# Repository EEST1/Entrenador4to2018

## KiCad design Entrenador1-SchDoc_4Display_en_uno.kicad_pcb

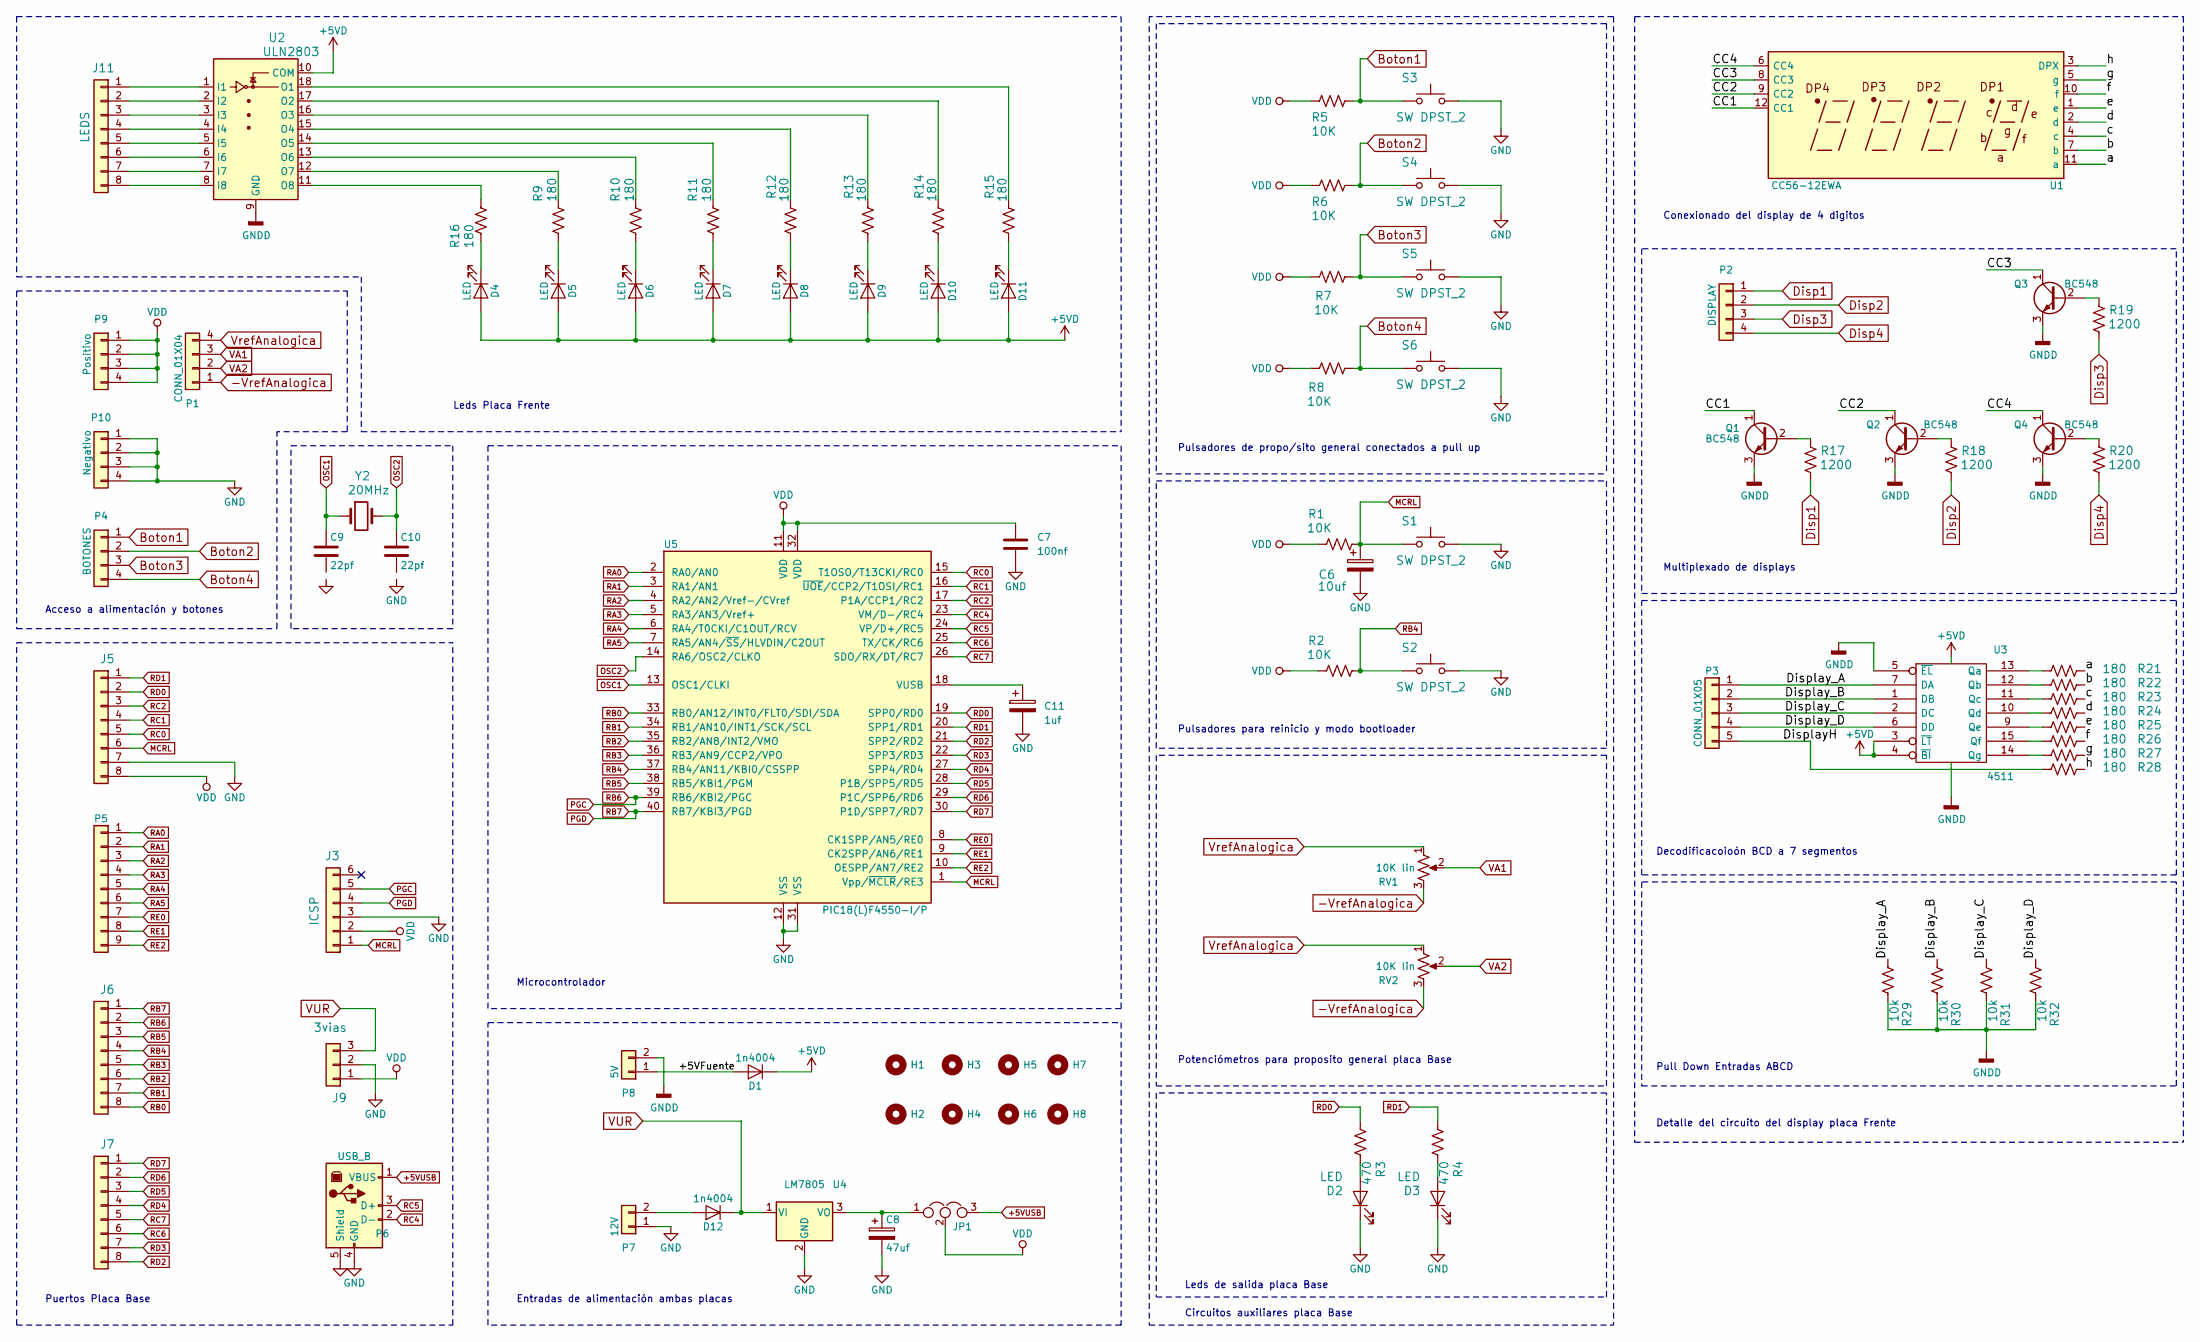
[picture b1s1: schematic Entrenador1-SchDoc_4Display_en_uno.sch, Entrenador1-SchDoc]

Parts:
C6: 10uf; CP_Radial_D6.3mm_P2.50mm
C7: 100nf; C_Disc_D5.0mm_W2.5mm_P2.50mm
C8: 47uf; CP_Radial_D5.0mm_P2.50mm
C9, C10: 22pf; C_Disc_D5.0mm_W2.5mm_P2.50mm
C11: 1uf; CP_Radial_D5.0mm_P2.50mm
D1, D12: 1n4004; D_5W_P10.16mm_Horizontal
D2, D3, D4, D5, D6, D7, D8, D9, D10, D11: LED; LED_D3.0mm
H1, H2, H3, H4, H5, H6, H7, H8: MountingHole; MountingHole_3.2mm_M3
J3: ICSP; Socket_Strip_Straight_1x06_Pitch2.54mm
J5, J6, J7: CON8; Socket_Strip_Straight_1x08_Pitch2.54mm
J9: 3vias; Pin_Header_Straight_1x03_Pitch2.54mm
J11: LEDS; Socket_Strip_Straight_1x08_Pitch2.54mm
JP1: JUMPER3; Pin_Header_Straight_1x03_Pitch2.54mm
P1: CONN_01X04; Socket_Strip_Straight_1x04_Pitch2.54mm
P2: DISPLAY; Socket_Strip_Straight_1x04_Pitch2.54mm
P3: CONN_01X05; Socket_Strip_Straight_1x05_Pitch2.54mm
P4: BOTONES; Socket_Strip_Straight_1x04_Pitch2.54mm
P5: CONN_01X09; Socket_Strip_Straight_1x09_Pitch2.54mm
P6: USB_B
P7: 12V; TerminalBlock_bornier-2_P5.08mm
P8: 5V; TerminalBlock_bornier-2_P5.08mm
P9: Positivo; Socket_Strip_Straight_1x04_Pitch2.54mm
P10: Negativo; Socket_Strip_Straight_1x04_Pitch2.54mm
Q1, Q2, Q3, Q4: BC548; TO-92_Molded_Narrow
R1, R2, R5, R6, R7, R8: 10K; R_Axial_DIN0207_L6.3mm_D2.5mm_P7.62mm_Horizontal
R3, R4: 470; R_Axial_DIN0207_L6.3mm_D2.5mm_P7.62mm_Horizontal
R9, R10, R11, R12, R13, R14, R15, R16, R21, R22, R23, R24, R25, R26, R27, R28: 180; R_Axial_DIN0207_L6.3mm_D2.5mm_P7.62mm_Horizontal
R17, R18, R19, R20: 1200; R_Axial_DIN0207_L6.3mm_D2.5mm_P7.62mm_Horizontal
R29, R30, R31, R32: 10k; R_Axial_DIN0207_L6.3mm_D2.5mm_P7.62mm_Horizontal
RV1, RV2: 10K lin; Potentiometer_Omeg_PC16PU_Horizontal
S1, S2, S3, S4, S5, S6: SW DPST_2; SW_PUSH_6mm_h13mm
U1: CC56-12EWA; CA56-12EWA
U2: ULN2803; DIP-18_W7.62mm_LongPads
U3: 4511; DIP-16_W7.62mm
U4: LM7805; TO-220-3_Vertical
U5: PIC18(L)F4550-I/P; DIP-40_W15.24mm_LongPads
Y2: 20MHz; Crystal_HC49-4H_Vertical

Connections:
+5VD: D1.1 (K), D4.2 (A), D5.2 (A), D6.2 (A), D7.2 (A), D8.2 (A), D9.2 (A), D10.2 (A), D11.2 (A), U2.10 (COM), U3.3 (~LT), U3.4 (~BI), U3.16 (Vdd)
+5VUSB: JP1.3, P6.1 (VBUS)
-VrefAnalogica: P1.1, RV1.3, RV2.3
/+5VFuente: D1.2 (A), P8.1
/CC1: Q1.1 (C), U1.12 (CC1)
/CC2: Q2.1 (C), U1.9 (CC2)
/CC3: Q3.1 (C), U1.8 (CC3)
/CC4: Q4.1 (C), U1.6 (CC4)
/DisplayH: P3.5, R28.2
/Display_A: P3.1, R29.1, U3.7 (DA)
/Display_B: P3.2, R30.1, U3.1 (DB)
/Display_C: P3.3, R31.1, U3.2 (DC)
/Display_D: P3.4, R32.1, U3.6 (DD)
/a: R21.1, U1.11 (a)
/b: R22.1, U1.7 (b)
/c: R23.1, U1.4 (c)
/d: R24.1, U1.2 (d)
/e: R25.1, U1.1 (e)
/f: R26.1, U1.10 (f)
/g: R27.1, U1.5 (g)
/h: R28.1, U1.3 (DPX)
Boton1: P4.1, R5.2, S3.1
Boton2: P4.2, R6.2, S4.1
Boton3: P4.3, R7.1, S5.1
Boton4: P4.4, R8.1, S6.1
Disp1: P2.1, R17.2
Disp2: P2.2, R18.2
Disp3: P2.3, R19.2
Disp4: P2.4, R20.2
GND: C6.2, C7.2, C8.2, C11.2, D2.1 (K), D3.1 (K), J3.3, J5.7, J9.2, P6.4 (GND), P6.5 (Shield), P7.1, P10.1, P10.2, P10.3, P10.4, S1.2, S2.2, S3.2, S4.2, S5.2, S6.2, U4.2 (GND), U5.12 (VSS), U5.31 (VSS)
GNDD: P8.2, Q1.3 (E), Q2.3 (E), Q3.3 (E), Q4.3 (E), R29.2, R30.2, R31.2, R32.2, U2.9 (GND), U3.5 (~EL), U3.8 (Vss)
MCRL: C6.1, J3.1, J5.6, R1.1, S1.1, U5.1 (Vpp/~MCLR~/RE3)
unnamed: C8.1, JP1.1, U4.3 (VO)
unnamed: C11.1, U5.18 (VUSB)
unnamed: D2.2 (A), R3.2
unnamed: D3.2 (A), R4.2
unnamed: D4.1 (K), R16.1
unnamed: D5.1 (K), R9.1
unnamed: D6.1 (K), R10.1
unnamed: D7.1 (K), R11.1
unnamed: D8.1 (K), R12.1
unnamed: D9.1 (K), R13.1
unnamed: D10.1 (K), R14.1
unnamed: D11.1 (K), R15.1
unnamed: D12.2 (A), P7.2
unnamed: J11.1, U2.1 (I1)
unnamed: J11.2, U2.2 (I2)
unnamed: J11.3, U2.3 (I3)
unnamed: J11.4, U2.4 (I4)
unnamed: J11.5, U2.5 (I5)
unnamed: J11.6, U2.6 (I6)
unnamed: J11.7, U2.7 (I7)
unnamed: J11.8, U2.8 (I8)
unnamed: Q1.2 (B), R17.1
unnamed: Q2.2 (B), R18.1
unnamed: Q3.2 (B), R19.1
unnamed: Q4.2 (B), R20.1
unnamed: R9.2, U2.12 (O7)
unnamed: R10.2, U2.13 (O6)
unnamed: R11.2, U2.14 (O5)
unnamed: R12.2, U2.15 (O4)
unnamed: R13.2, U2.16 (O3)
unnamed: R14.2, U2.17 (O2)
unnamed: R15.2, U2.18 (O1)
unnamed: R16.2, U2.11 (O8)
unnamed: R21.2, U3.13 (Qa)
unnamed: R22.2, U3.12 (Qb)
unnamed: R23.2, U3.11 (Qc)
unnamed: R24.2, U3.10 (Qd)
unnamed: R25.2, U3.9 (Qe)
unnamed: R26.2, U3.15 (Qf)
unnamed: R27.2, U3.14 (Qg)
OSC1: C9.1, U5.13 (OSC1/CLKI), Y2.1
OSC2: C10.1, U5.14 (RA6/OSC2/CLKO), Y2.2
PGC: J3.5, J6.2, U5.39 (RB6/KBI2/PGC)
PGD: J3.4, J6.1, U5.40 (RB7/KBI3/PGD)
RA0: P5.1, U5.2 (RA0/AN0)
RA1: P5.2, U5.3 (RA1/AN1)
RA2: P5.3, U5.4 (RA2/AN2/Vref-/CVref)
RA3: P5.4, U5.5 (RA3/AN3/Vref+)
RA4: P5.5, U5.6 (RA4/T0CKI/C1OUT/RCV)
RA5: P5.6, U5.7 (RA5/AN4/~SS~/HLVDIN/C2OUT)
RB0: J6.8, U5.33 (RB0/AN12/INT0/FLT0/SDI/SDA)
RB1: J6.7, U5.34 (RB1/AN10/INT1/SCK/SCL)
RB2: J6.6, U5.35 (RB2/AN8/INT2/VMO)
RB3: J6.5, U5.36 (RB3/AN9/CCP2/VPO)
RB4: J6.4, R2.1, S2.1, U5.37 (RB4/AN11/KBI0/CSSPP)
RB5: J6.3, U5.38 (RB5/KBI1/PGM)
RC0: J5.5, U5.15 (T1OSO/T13CKI/RC0)
RC1: J5.4, U5.16 (~UOE~/CCP2/T1OSI/RC1)
RC2: J5.3, U5.17 (P1A/CCP1/RC2)
RC4: P6.2 (D-), U5.23 (VM/D-/RC4)
RC5: P6.3 (D+), U5.24 (VP/D+/RC5)
RC6: J7.6, U5.25 (TX/CK/RC6)
RC7: J7.5, U5.26 (SDO/RX/DT/RC7)
RD0: J5.2, R3.1, U5.19 (SPP0/RD0)
RD1: J5.1, R4.1, U5.20 (SPP1/RD1)
RD2: J7.8, U5.21 (SPP2/RD2)
RD3: J7.7, U5.22 (SPP3/RD3)
RD4: J7.4, U5.27 (SPP4/RD4)
RD5: J7.3, U5.28 (P1B/SPP5/RD5)
RD6: J7.2, U5.29 (P1C/SPP6/RD6)
RD7: J7.1, U5.30 (P1D/SPP7/RD7)
RE0: P5.7, U5.8 (CK1SPP/AN5/RE0)
RE1: P5.8, U5.9 (CK2SPP/AN6/RE1)
RE2: P5.9, U5.10 (OESPP/AN7/RE2)
VA1: P1.3, RV1.2
VA2: P1.2, RV2.2
VDD: C7.1, J3.2, J5.8, J9.1, JP1.2, P9.1, P9.2, P9.3, P9.4, R1.2, R2.2, R5.1, R6.1, R7.2, R8.2, U5.11 (VDD), U5.32 (VDD)
VUR: D12.1 (K), J9.3, U4.1 (VI)
VrefAnalogica: P1.4, RV1.1, RV2.1

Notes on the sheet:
Decodificacoioón BCD a 7 segmentos
Pull Down Entradas ABCD
Pulsadores de propo/sito general conectados a pull up
Pulsadores para reinicio y modo bootloader
Potenciómetros para proposito general placa Base
Puertos Placa Base
Multiplexado de displays
Conexionado del display de 4 digitos
Entradas de alimentación ambas placas
Leds de salida placa Base
Acceso a alimentación y botones
Microcontrolador
Leds Placa Frente
Detalle del circuito del display placa Frente
Circuitos auxiliares placa Base

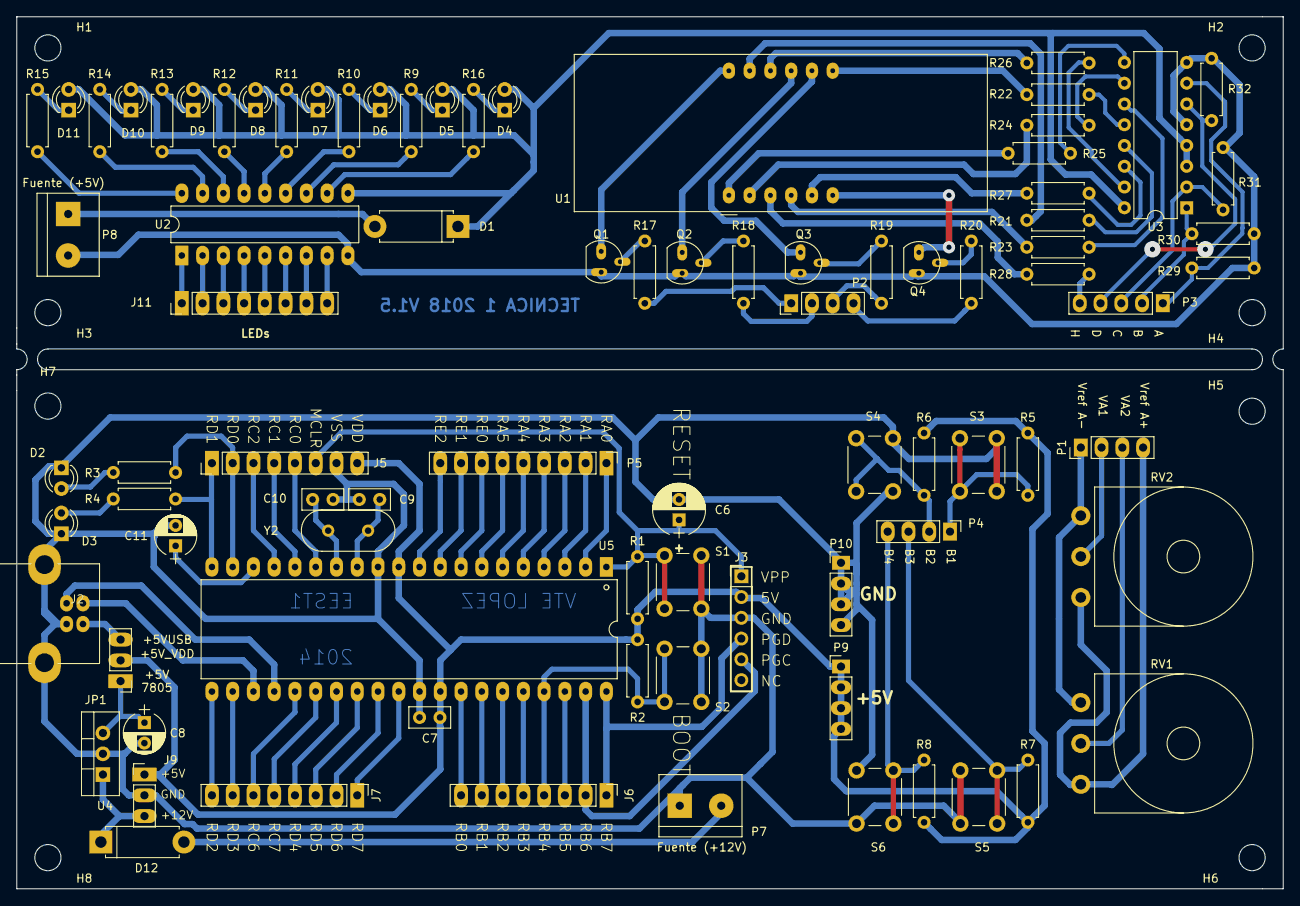
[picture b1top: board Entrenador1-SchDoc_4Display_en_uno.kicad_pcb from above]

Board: 2 copper layers, 154.9 x 106.7 mm, 93 parts (0 on the bottom side), 111 nets.

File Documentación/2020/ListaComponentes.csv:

Referencia,Cantidad,Value,Footprint
C10 C9,2,22pf,C_Disc_D5.0mm_W2.5mm_P2.50mm
C11,1,1uf,CP_Radial_D5.0mm_P2.50mm
C6,1,10uf,CP_Radial_D6.3mm_P2.50mm
C7,1,100nf,C_Disc_D5.0mm_W2.5mm_P2.50mm
C8,1,47uf,CP_Radial_D5.0mm_P2.50mm
D1 D12,2,1n4004,D_5W_P10.16mm_Horizontal
D11 D10 D9 D8 D7 D6 D5 D4 D3 D2,10,LED,LED_D3.0mm
J11,1,LEDS,Socket_Strip_Straight_1x08_Pitch2.54mm
J3,1,ICSP,Socket_Strip_Straight_1x06_Pitch2.54mm
J5 J6 J7,3,CON8,Socket_Strip_Straight_1x08_Pitch2.54mm
J9,1,3vias,Pin_Header_Straight_1x03_Pitch2.54mm
JP1,1,JUMPER3,Pin_Header_Straight_1x03_Pitch2.54mm
P1,1,CONN_01X04,Socket_Strip_Straight_1x04_Pitch2.54mm
P10,1,Negativo,Socket_Strip_Straight_1x04_Pitch2.54mm
P2,1,DISPLAY,Socket_Strip_Straight_1x04_Pitch2.54mm
P3,1,CONN_01X05,Socket_Strip_Straight_1x05_Pitch2.54mm
P4,1,BOTONES,Socket_Strip_Straight_1x04_Pitch2.54mm
P5,1,CONN_01X09,Socket_Strip_Straight_1x09_Pitch2.54mm
P6,1,USB_B,USB_B
P7,1,12V,TerminalBlock_bornier-2_P5.08mm
P8,1,5V,TerminalBlock_bornier-2_P5.08mm
P9,1,Positivo,Socket_Strip_Straight_1x04_Pitch2.54mm
Q4 Q3 Q2 Q1,4,BC548,TO-92_Molded_Narrow
R20 R19 R18 R17,4,1200,R_Axial_DIN0207_L6.3mm_D2.5mm_P7.62mm_Horizontal
R27 R26 R25 R24 R23 R22 R21 R16 R15 R14 R13 R12 R11 R10 R9 R28,16,180,R_Axial_DIN0207_L6.3mm_D2.5mm_P7.62mm_Horizontal
R3 R4,2,470,R_Axial_DIN0207_L6.3mm_D2.5mm_P7.62mm_Horizontal
R32 R31 R30 R29,4,10k,R_Axial_DIN0207_L6.3mm_D2.5mm_P7.62mm_Horizontal
R8 R7 R6 R5 R1 R2,6,10K,R_Axial_DIN0207_L6.3mm_D2.5mm_P7.62mm_Horizontal
RV1 RV2,2,10K lin,Potentiometer_Omeg_PC16PU_Horizontal
S6 S5 S4 S3 S2 S1,6,SW DPST_2,SW_PUSH_6mm_h13mm
U1,1,CC56-12EWA,CA56-12EWA
U2,1,ULN2803,DIP-18_W7.62mm_LongPads
U3,1,CD4511,DIP-16_W7.62mm
U4,1,LM7805,TO-220-3_Vertical
U5,1,PIC18(L)F4550-I/P,DIP-40_W15.24mm_LongPads
Y2,1,20MHz,Crystal_HC49-4H_Vertical

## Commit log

2018-02-05 Initial commit
    Changes to be committed:
    new file: Base.kicad_pcb-bak
    new file: Entrenador1-SchDoc-cache.lib
    new file: Entrenador1-SchDoc-rescue.lib
    new file: Entrenador1-SchDoc.bak
    new file: Entrenador1-SchDoc.cmp
2018-02-05 Set theme jekyll-theme-slate
2018-02-05 en proceso de creación
2018-02-05 adición del BOM
2018-02-05 ajustes BOM
2018-02-06 se agrandan PADS
2018-02-07 cambio de huellas transistores, ajuste de pistas según prototipo
2018-02-09 En base al prototipo, se replantean las posiciones de los elementos
2018-02-10 Se agrega un diodo de protección a la placa de visualización Se eliminan los pines extra de alimentación de la placa de visualización
2018-02-14 se separan las placas de frente y base
2018-02-14 se agregan los archivos de BAse y Frente
2018-02-14 Se modifica el gabinete
2018-02-24 Bugs en PCNEW
2018-02-24 Avances sobre el gabinete
2018-02-26 Se agregan los orificios de fijación basados en el prototipo real
2018-03-02 Se realizan las perforaciones de fijaci[on frontal
2018-03-16 se cambia de posición el teclado
2018-03-24 Diseño definitivo con desplazamiento USB
2018-03-24 Pequeños ajustes repecto de las capas de información en el PCB
2018-03-25 Arreglos y ajuste
2018-07-24 modified: Entrenador1-SchDoc.net modified: Entrenador1-SchDoc.sch Untracked files: Entrenador1-SchDoc_4Display_en_uno.kicad_pcb Entrenador1-SchDoc_4Display_en_uno.kicad_pcb-bak
2018-07-24 Changes to be committed: new file: Entrenador1-SchDoc_4Display_en_uno.kicad_pcb new file: Entrenador1-SchDoc_4Display_en_uno.kicad_pcb-bak new file: Entrenador1-SchDoc_4Display_en_uno.pro
2018-11-04 CAmbios en el conector USB aumento de los PADs On branch master Your branch is up to date with 'origin/master'.
    Changes to be committed:
    modified: libreria.pretty/USB_B.kicad_mod
    Untracked files:
    GerberOutput/Entrenador1-SchDoc_4Display_en_uno-Cmts.User.pdf
    GerberOutput/Entrenador1-SchDoc_4Display_en_uno-Dwgs.User.pdf
    GerberOutput/Entrenador1-SchDoc_4Display_en_uno-Edge.Cuts.pdf
2018-11-04 Se modifica el conector USB para un mejor trabajo de los chicos
2018-11-04 Actualización de la placa con nuevos componentes
2018-11-19 new file: Gabinete2/basenameplate.gcode new file: Gabinete2/basenameplate.stl new file: Gabinete2/basenameplate.x3g new file: Gabinete2/letranegranameplate.stl new file: Gabinete2/nameplate.FCStd new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
2018-11-19 new file: Gabinete2/Perilla.FCStd new file: Gabinete2/Perilla.FCStd1 new file: Gabinete2/PerillaCompleta001 (Meshed).stl modified: Gabinete2/nameplate.FCStd modified: Gabinete2/nameplate.FCStd1 new f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
2018-11-19 modified: Gabinete2/PerillaCompleta001 (Meshed).stl modified: Gabinete2/perilla.gcode modified: Gabinete2/perilla.x3g
2018-11-20 modified: Gabinete2/Perilla.FCStd modified: Gabinete2/Perilla.FCStd1
2018-11-21 modified: Gabinete2/nameplate.FCStd modified: Gabinete2/nameplate.FCStd1 renamed: Gabinete2/perilla2.stl -> Gabinete2/perilla2lemos.stl renamed: Gabinete2/perilla.x3g -> Gabinete2/perillalemos.x3g
2019-06-22 Changes to be committed: modified: Gabinete2/basenameplate.stl new file: Gabinete2/letrabordes.stl modified: Gabinete2/letranegranameplate.stl modified: Gabinete2/nameplate.FCStd modified: Gabinete2/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
2019-06-22 modified: Entrenador1-SchDoc-cache.lib modified: Entrenador1-SchDoc-rescue.lib modified: Entrenador1-SchDoc.bak modified: Entrenador1-SchDoc.net modified: Entrenador1-SchDoc.pro modified: Entrenador1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
2019-06-22 modified: Entrenador1-SchDoc_4Display_en_uno.bak modified: Entrenador1-SchDoc_4Display_en_uno.kicad_pcb modified: Entrenador1-SchDoc_4Display_en_uno.kicad_pcb-bak modified: Entrenador1-SchDoc_4Displa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
2019-06-22 modified: Entrenador1-SchDoc_4Display_en_uno-cache.lib modified: Entrenador1-SchDoc_4Display_en_uno.bak modified: Entrenador1-SchDoc_4Display_en_uno.kicad_pcb modified: Entrenador1-SchDoc_4Display_en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
2019-06-26 nuevo archivo: Entrenador1-SchDoc_4Display_en_uno-panel.kicad_pcb nuevo archivo: Entrenador1-SchDoc_4Display_en_uno-panel.kicad_pcb-bak nuevo archivo: Entrenador1-SchDoc_4Display_en_uno-panel.pro nue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
2019-12-28 Se realizaron cambios en el PCB respecto de los modelos 3D
2019-12-29 Ajuste de modelos step parte 1
2019-12-29 corrección modelos 3d
2019-12-29 Changes to be committed: modified: Entrenador1-SchDoc_4Display_en_uno.kicad_pcb modified: Entrenador1-SchDoc_4Display_en_uno.kicad_pcb-bak modified: Entrenador1-SchDoc_4Display_en_uno.step deleted: _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
2019-12-29 Changes to be committed: modified: fp-info-cache modified: libreria.pretty/USB_B.kicad_mod
2019-12-31 deleted: Entrenador1-SchDoc.net modified: Entrenador1-SchDoc_4Display_en_uno-cache.lib modified: Entrenador1-SchDoc_4Display_en_uno.kicad_pcb modified: Entrenador1-SchDoc_4Display_en_uno.kicad_pcb-ba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
2019-12-31 Changes to be committed: modified: Entrenador1-SchDoc_4Display_en_uno-cache.lib modified: Entrenador1-SchDoc_4Display_en_uno.kicad_pcb modified: Entrenador1-SchDoc_4Display_en_uno.kicad_pcb-bak modif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
2019-12-31 modified: Entrenador1-SchDoc_4Display_en_uno-cache.lib modified: Entrenador1-SchDoc_4Display_en_uno.kicad_pcb modified: Entrenador1-SchDoc_4Display_en_uno.kicad_pcb-bak modified: Entrenador1-SchDoc_4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
2019-12-31 deleted: rescue-backup/Entrenador1-SchDoc-2019-06-22-08-57-40.pro deleted: rescue-backup/Entrenador1-SchDoc-2019-06-22-08-57-40.sch deleted: rescue-backup/Entrenador1-SchDoc-cache-2019-06-22-08-57-40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
2020-01-16 new file: "Documentaci\303\263n/2020/Principal.tex" new file: "Documentaci\303\263n/2020/imagenes/Clasif_Semic-eps-converted-to.pdf" new file: "Documentaci\303\263n/2020/imagenes/Clasif_Semic.eps" ne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
2020-01-29 Changes to be committed: new file: "Documentaci\303\263n/2020/Armado.aux" new file: "Documentaci\303\263n/2020/Armado.tex" new file: "Documentaci\303\263n/2020/Introduccion.aux" new file: "Documentac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
2020-01-30 Changes to be committed: new file: "Documentaci\303\263n/2020/.~lock.ListaComponentes.csv#" modified: "Documentaci\303\263n/2020/Armado.aux" modified: "Documentaci\303\263n/2020/Armado.tex" new file: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
2020-01-31 Changes to be committed: new file: Circuito2.sch deleted: "Documentaci\303\263n/2020/.~lock.ListaComponentes.csv#" modified: "Documentaci\303\263n/2020/Armado.aux" modified: "Documentaci\303\263n/202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
2020-02-04 Changes to be committed: deleted: Circuito2.sch modified: "Documentaci\303\263n/2020/Armado.aux" modified: "Documentaci\303\263n/2020/Armado.tex" modified: "Documentaci\303\263n/2020/Principal.aux" m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
2020-02-06 Changes to be committed: new file: "Documentaci\303\263n/2020/CAM_AcrilicoEntrenador.nc"
2020-02-09 Changes to be committed: new file: CAM/Entrenador2020.FlatPrj new file: "Documentaci\303\263n/2020/CAM_AcrilicoEntrenador_2.nc" new file: "Documentaci\303\263n/2020/CAM_AcrilicoEntrenador_3.nc" modif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
2020-02-09 Changes to be committed: new file: CAM/Entrenador1-SchDoc_4Display_en_uno-B_Cu.gbr_panelized_iso_cnc.nc new file: CAM/Entrenador1-SchDoc_4Display_en_uno-Edge_Cuts.gbr_panelized_cutout_cnc.nc new file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
2020-02-11 Changes to be committed: new file: "Documentaci\303\263n/2020/CAM_AcrilicoEntrenador_4.nc"
2020-02-22 new file: CAM/acrilico.nc
2020-02-24 Changes to be committed: renamed: "Documentaci\303\263n/2020/CAM_AcrilicoEntrenador.nc" -> "Documentaci\303\263n/2020/CAM/CAM_AcrilicoEntrenador.nc" renamed: "Documentaci\303\263n/2020/CAM_AcrilicoEn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
2020-04-26 Changes to be committed: new file: CAM/1001.nc new file: "Documentaci\303\263n/2020/CAM_AcrilicoEntrenador.nc" renamed: Film/Entrenador1-SchDoc_4Display_en_uno-B_Cu.gbr_panelized.svg -> "Documentaci\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
2021-01-28 new file: "Documentaci\303\263n/FB_IMG_1604214108332.jpg" modified: fp-info-cache
